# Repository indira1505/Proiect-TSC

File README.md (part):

INK TIME SMARTWATCH

1. DIAGRAMA COMPONENTE
    Acesta este un proiect de ceas inteligent bazat pe arhitectura nRF52840, echipat cu un ecran
e-Paper pentru consum redus și un sistem de alertă haptică.

2. Bill Of Materials

| Qty | Value                                  | Device                                                                       | Package                                                                                                                | Parts                                                                                                                      | Description                                                                                                               | ARROW_PART_NUMBER | ARROW_PRICE-STOCK                                                                                | AVAILABILITY | CHECK_PRICES                                                                       | COPYRIGHT                                                | DESCRIPTION                                                                                              | HEIGHT                                   | JLCPCB      | MANUFACTURER_NAME                                 | MANUFACTURER_PART_NUMBER                                         | MF                 | MFR_NAME          | MOUSER_PART_NUMBER | MOUSER_PRICE-STOCK                                                                                           | MP                                                                                                       | PACKAGE                     | POPULARITY | PRICE            | PROD_ID                      | PURCHASE-URL                                                                                                                               | SNAPEDA_LINK                                                                      | TP_SIGNAL_NAME | U1                                                                                                                                              | VALUE                                                                               |
|-----|----------------------------------------|------------------------------------------------------------------------------|------------------------------------------------------------------------------------------------------------------------|----------------------------------------------------------------------------------------------------------------------------|---------------------------------------------------------------------------------------------------------------------------|-------------------|--------------------------------------------------------------------------------------------------|--------------|------------------------------------------------------------------------------------|----------------------------------------------------------|----------------------------------------------------------------------------------------------------------|------------------------------------------|-------------|---------------------------------------------------|------------------------------------------------------------------|--------------------|-------------------|--------------------|--------------------------------------------------------------------------------------------------------------|----------------------------------------------------------------------------------------------------------|-----------------------------|------------|------------------|------------------------------|--------------------------------------------------------------------------------------------------------------------------------------------|-----------------------------------------------------------------------------------|----------------|-------------------------------------------------------------------------------------------------------------------------------------------------|-------------------------------------------------------------------------------------|
| 1   | RT6160AWSC                             | RT6160AWSC_RT6160AWSC                                                        | RT6160AWSC_BGA15C40P3X5_140X230X60                                                                                     | IC9                                                                                                                        | Buck-Boost Regulator Positive Output Step-Up/Step-Down I2C DC-DC Controller IC 15-WL-CSP (BSC) (1.4x2.3)                  |                   |                                                                                                  |              |                                                                                    |                                                          | Buck-Boost Regulator Positive Output Step-Up/Step-Down I2C DC-DC Controller IC 15-WL-CSP (BSC) (1.4x2.3) | 0.6mm                                    |             | RICHTEK                                           | RT6160AWSC                                                       |                    |                   | 835-RT6160AWSC     | https://www.mouser.co.uk/ProductDetail/Richtek/RT6160AWSC?qs=amGC7iS6iy%2FLd9PSoixZXQ%3D%3D                  |                                                                                                          |                             |            |                  |                              |                                                                                                                                            |                                                                                   |                |                                                                                                                                                 |                                                                                     |
| 1   | SI1308EDL-T1-GE3                       | ESP32_C6_LIBRARY_6_SI1308EDL-T1-GE3                                          | ESP32_C6_LIBRARY_6_SOT65P210X110-3N                                                                                    | Q3                                                                                                                         | MOSFET N-Ch 30V 1.5A TrenchFET SC70 Vishay Si1308EDL-T1-GE3 N-channel MOSFET Transistor, 1.5 A, 30 V, 3-Pin SC-70         |                   |                                                                                                  | In Stock     | https://www.snapeda.com/parts/SI1308EDL-T1-GE3/Vishay+Siliconix/view-part/?ref=eda |                                                          | Si1308EDL-T1-GE3 N-channel MOSFET Transistor                                                             | 1.5 A                                    | 30 V        | 3-Pin SC-70 | Siliconix / Vishay SI1308EDL-T1-GE3 |                                                                  |                    |                   |                    | Vishay Siliconix                                                                                             |                                                                                                          |                             |            | SI1308EDL-T1-GE3 | SOT-323 Vishay Semiconductor |                                                                                                                                            | None                                                                              |                | https://www.snapeda.com/api/url_track_click_mouser/?unipart_id=274603&manufacturer=Vishay Siliconix&part_name=SI1308EDL-T1-GE3&search_term=None | https://www.snapeda.com/parts/SI1308EDL-T1-GE3/Vishay+Siliconix/view-part/?ref=snap |
| 1   | TC2030-IDC                             | TC2030-IDC_TC2030-IDC                                                        | TC2030-IDC_TC2030IDC                                                                                                   | J2                                                                                                                         | CABLE ADAPTER 6 POS                                                                                                       |                   |                                                                                                  |              |                                                                                    |                                                          | CABLE ADAPTER 6 POS                                                                                      | 19mm                                     |             | Tag Connect                                       | TC2030-IDC                                                       |                    |                   |                    |                                                                                                              |                                                                                                          |                             |            |                  |                              |                                                                                                                                            |                                                                                   |                |                                                                                                                                                 |                                                                                     |
| 1   | USBLC6-2SC6Y                           | ESP32_C6_LIBRARY_3_USBLC6-2SC6Y                                              | ESP32_C6_LIBRARY_3_SOT95P280X145-6N                                                                                    | D3                                                                                                                         | Low Cap. ESD Protection Auto SOT-23-6 STMicroelectronics USBLC6-2SC6Y, Dual Uni-Directional TVS Diode Array, 6-Pin SOT-23 |                   |                                                                                                  | In Stock     | https://www.snapeda.com/parts/USBLC6-2SC6Y/STMicroelectronics/view-part/?ref=eda   |                                                          | 17V Clamp 5A (8/20µs) Ipp Tvs Diode Surface Mount SOT-23-6                                               |                                          |             |                                                   |                                                                  | STMicroelectronics |                   |                    |                                                                                                              | USBLC6-2SC6Y                                                                                             | SOT-23-6 STMicroelectronics |            | None             |                              |                                                                                                                                            | https://www.snapeda.com/parts/USBLC6-2SC6Y/STMicroelectronics/view-part/?ref=snap |                |                                                                                                                                                 |                                                                                     |
| 1   | 0.1uF/50V                              | NORDIC_NRF_3_CAPACITOR_0201_L                                                | NORDIC_NRF_3_RESC0201_L                                                                                                | EPD_C5                                                                                                                     | Generic chip capacitor                                                                                                    |                   |                                                                                                  |              |                                                                                    |                                                          |                                                                                                          |                                          |             |                                                   |                                                                  |                    |                   |                    |                                                                                                              |                                                                                                          |                             |            |                  |                              |                                                                                                                                            |                                                                                   |                |                                                                                                                                                 |                                                                                     |
| 1   | 0.47                                   | CPF0201D7K68C1_CPF0201D7K68C1                                                | CPF0201D7K68C1_0201                                                                                                    | R1_EP_DR                                                                                                                   | 7.68k 0201 Thin Film Surface Mount Fixed Resistor +/-0.5% 0.031W CPF0201D7K68C1                                           |                   |                                                                                                  |              |                                                                                    |                                                          |                                                                                                          |                                          |             |                                                   |                                                                  |                    |                   |                    |                                                                                                              |                                                                                                          |                             |            |                  |                              |                                                                                                                                            |                                                                                   |                |                                                                                                                                                 |                                                                                     |
| 1   | 1.0µF                                  | NORDIC_NRF_3_CAPACITOR_0201_L                                                | NORDIC_NRF_3_RESC0201_L                                                                                                | C15                                                                                                                        | Generic chip capacitor                                                                                                    |                   |                                                                                                  |              |                                                                                    |                                                          |                                                                                                          |                                          |             |                                                   |                                                                  |                    |                   |                    |                                                                                                              |                                                                                                          |                             |            |                  |                              |                                                                                                                                            |                                                                                   |                |                                                                                                                                                 |                                                                                     |
| 5   | 100nF                                  | NORDIC_NRF_3_CAPACITOR_0201_L                                                | NORDIC_NRF_3_RESC0201_L                                                                                                | C5, C7, C8, C12, C19                                                                                                       | Generic chip capacitor                                                                                                    |                   |                                                                                                  |              |                                                                                    |                                                          |                                                                                                          |                                          |             |                                                   |                                                                  |                    |                   |                    |                                                                                                              |                                                                                                          |                             |            |                  |                              |                                                                                                                                            |                                                                                   |                |                                                                                                                                                 |                                                                                     |
| 1   | 100pF                                  | NORDIC_NRF_3_CAPACITOR_0201_L                                                | NORDIC_NRF_3_RESC0201_L                                                                                                | C11                                                                                                                        | Generic chip capacitor                                                                                                    |                   |                                                                                                  |              |                                                                                    |                                                          |                                                                                                          |                                          |             |                                                   |                                                                  |                    |                   |                    |                                                                                                              |                                                                                                          |                             |            |                  |                              |                                                                                                                                            |                                                                                   |                |                                                                                                                                                 |                                                                                     |
| 4   | 0.1uF                                  | GRM011R60J152KE01L_2_GRM011R60J152KE01L                                      | GRM011R60J152KE01L_2_CAPC0201X13N                                                                                      | C23, C27, C34, C42                                                                                                         | Check availability                                                                                                        |                   |                                                                                                  | In Stock     | https://www.snapeda.com/parts/GRM011R60J152KE01L/Murata/view-part/?ref=eda         |                                                          | SMD Capacitor X5R(EIA) with Capacitance: 1500pF Tol. 10%. Rated Voltage: 6.3Vdc                          |                                          |             |                                                   |                                                                  | Murata             |                   |                    |                                                                                                              | GRM011R60J152KE01L                                                                                       | 0201 Murata                 |            | None             |                              |                                                                                                                                            | https://www.snapeda.com/parts/GRM011R60J152KE01L/Murata/view-part/?ref=snap       |                |                                                                                                                                                 |                                                                                     |
| 3   | 10K                                    | CPF0201D7K68C1_CPF0201D7K68C1                                                | CPF0201D7K68C1_0201                                                                                                    | R2_EP_DR, R9, R_PWR_EPD                                                                                                    | 7.68k 0201 Thin Film Surface Mount Fixed Resistor +/-0.5% 0.031W CPF0201D7K68C1                                           |                   |                                                                                                  |              |                                                                                    |                                                          |                                                                                                          |                                          |             |                                                   |                                                                  |                    |                   |                    |                                                                                                              |                                                                                                          |                             |            |                  |                              |                                                                                                                                            |                                                                                   |                |                                                                                                                                                 |                                                                                     |
| 3   | 10K                                    | ERA-1AEB3401C_CPF0201D7K68C1                                                 | ERA-1AEB3401C_0201                                                                                                     | R5, R7, R8                                                                                                                 | 7.68k 0201 Thin Film Surface Mount Fixed Resistor +/-0.5% 0.031W CPF0201D7K68C1                                           |                   |                                                                                                  |              |                                                                                    |                                                          |                                                                                                          |                                          |             |                                                   |                                                                  |                    |                   |                    |                                                                                                              |                                                                                                          |                             |            |                  |                              |                                                                                                                                            |                                                                                   |                |                                                                                                                                                 |                                                                                     |
| 1   | 10uF                                   | NORDIC_NRF_3_CAPACITOR_0201_L                                                | NORDIC_NRF_3_RESC0201_L                                                                                                | C1-EP-DR                                                                                                                   | Generic chip capacitor                                                                                                    |                   |                                                                                                  |              |                                                                                    |                                                          |                                                                                                          |                                          |             |                                                   |                                                                  |                    |                   |                    |                                                                                                              |                                                                                                          |                             |            |                  |                              |                                                                                                                                            |                                                                                   |                |                                                                                                                                                 |                                                                                     |
| 2   | 10uF                                   | PERFECT_0402_CAP_0402                                                        | PERFECT_0402_0402                                                                                                      | C24, C39                                                                                                                   | 0402 (1005 Metric)                                                                                                        |                   |                                                                                                  |              |                                                                                    |                                                          |                                                                                                          |                                          |             |                                                   |                                                                  |                    |                   |                    |                                                                                                              |                                                                                                          |                             |            |                  |                              |                                                                                                                                            |                                                                                   |                |                                                                                                                                                 |                                                                                     |
| 1   |                                        | ESP32_C6_LIBRARY_7_JUMPER_SJ                                                 | ESP32_C6_LIBRARY_7_JUMPER_SJ                                                                                           | SJ1                                                                                                                        | SMD solder JUMPER                                                                                                         |                   |                                                                                                  |              |                                                                                    |                                                          |                                                                                                          |                                          |             |                                                   |                                                                  |                    |                   |                    |                                                                                                              |                                                                                                          |                             | 3          |                  |                              |                                                                                                                                            |                                                                                   |                |                                                                                                                                                 |                                                                                     |
| 3   | 0                                      | CPF0201D7K68C1_CPF0201D7K68C1                                                | CPF0201D7K68C1_0201                                                                                                    | R2, R3, R4                                                                                                                 | 7.68k 0201 Thin Film Surface Mount Fixed Resistor +/-0.5% 0.031W CPF0201D7K68C1                                           |                   |                                                                                                  |              |                                                                                    |                                                          |                                                                                                          |                                          |             |                                                   |                                                                  |                    |                   |                    |                                                                                                              |                                                                                                          |                             |            |                  |                              |                                                                                                                                            |                                                                                   |                |                                                                                                                                                 |                                                                                     |
| 1   | 10µH                                   | NORDIC_NRF_2_INDUCTOR_0402_L                                                 | NORDIC_NRF_2_RESC0402_L                                                                                                | L2                                                                                                                         | Generic chip inductor                                                                                                     |                   |                                                                                                  |              |                                                                                    |                                                          |                                                                                                          |                                          |             |                                                   |                                                                  |                    |                   |                    |                                                                                                              |                                                                                                          |                             |            |                  |                              |                                                                                                                                            |                                                                                   |                |                                                                                                                                                 |                                                                                     |
| 4   | 12pF                                   | NORDIC_NRF_3_CAPACITOR_0201_L                                                | NORDIC_NRF_3_RESC0201_L                                                                                                | C1, C2, C17, C18                                                                                                           | Generic chip capacitor                                                                                                    |                   |                                                                                                  |              |                                                                                    |                                                          |                                                                                                          |                                          |             |                                                   |                                                                  |                    |                   |                    |                                                                                                              |                                                                                                          |                             |            |                  |                              |                                                                                                                                            |                                                                                   |                |                                                                                                                                                 |                                                                                     |
| 1   | 15nH                                   | NORDIC_NRF_2_INDUCTOR_0402_L                                                 | NORDIC_NRF_2_RESC0402_L                                                                                                | L3                                                                                                                         | Generic chip inductor                                                                                                     |                   |                                                                                                  |              |                                                                                    |                                                          |                                                                                                          |                                          |             |                                                   |                                                                  |                    |                   |                    |                                                                                                              |                                                                                                          |                             |            |                  |                              |                                                                                                                                            |                                                                                   |                |                                                                                                                                                 |                                                                                     |
| 2   | 1pF                                    | NORDIC_NRF_3_CAPACITOR_0201_L                                                | NORDIC_NRF_3_RESC0201_L                                                                                                | C3, C4                                                                                                                     | Generic chip capacitor                                                                                                    |                   |                                                                                                  |              |                                                                                    |                                                          |                                                                                                          |                                          |             |                                                   |                                                                  |                    |                   |                    |                                                                                                              |                                                                                                          |                             |            |                  |                              |                                                                                                                                            |                                                                                   |                |                                                                                                                                                 |                                                                                     |
| 6   | 1uF                                    | GRM011R60J152KE01L_2_GRM011R60J152KE01L                                      | GRM011R60J152KE01L_2_CAPC0201X13N                                                                                      | C29, C30, C31, C32, C37, C38                                                                                               | Check availability                                                                                                        |                   |                                                                                                  | In Stock     | https://www.snapeda.com/parts/GRM011R60J152KE01L/Murata/view-part/?ref=eda         |                                                          | SMD Capacitor X5R(EIA) with Capacitance: 1500pF Tol. 10%. Rated Voltage: 6.3Vdc                          |                                          |             |                                                   |                                                                  | Murata             |                   |                    |                                                                                                              | GRM011R60J152KE01L                                                                                       | 0201 Murata                 |            | None             |                              |                                                                                                                                            | https://www.snapeda.com/parts/GRM011R60J152KE01L/Murata/view-part/?ref=snap       |                |                                                                                                                                                 |                                                                                     |
| 9   | 1uF/50V                                | NORDIC_NRF_3_CAPACITOR_0201_L                                                | NORDIC_NRF_3_RESC0201_L                                                                                                | EPD_C1, EPD_C2, EPD_C6, EPD_C7, EPD_C8, EPD_C9, EPD_C10, EPD_C11, EPD_C12                                                  | Generic chip capacitor                                                                                                    |                   |                                                                                                  |              |                                                                                    |                                                          |                                                                                                          |                                          |             |                                                   |                                                                  |                    |                   |                    |                                                                                                              |                                                                                                          |                             |            |                  |                              |                                                                                                                                            |                                                                                   |                |                                                                                                                                                 |                                                                                     |
| 1   | 2.2                                    | CPF0201D7K68C1_CPF0201D7K68C1                                                | CPF0201D7K68C1_0201                                                                                                    | R_TYPE_SEL                                                                                                                 | 7.68k 0201 Thin Film Surface Mount Fixed Resistor +/-0.5% 0.031W CPF0201D7K68C1                                           |                   |                                                                                                  |              |                                                                                    |                                                          |                                                                                                          |                                          |             |                                                   |                                                                  |                    |                   |                    |                                                                                                              |                                                                                                          |                             |            |                  |                              |                                                                                                                                            |                                                                                   |                |                                                                                                                                                 |                                                                                     |
| 3   | 2025-10-22_07-23-44_LIBRARY_EVP-AKE31A | 2025-10-22_07-23-44_LIBRARY_EVP-AKE31A                                       | 2025-10-22_07-23-44_LIBRARY_SW_EVP-AKE31A_PAN                                                                          | SW_DN, SW_ENT, SW_UP                                                                                                       |                                                                                                                           |                   |                                                                                                  |              |                                                                                    |                                                          |                                                                                                          |                                          |             |                                                   |                                                                  |                    |                   |                    |                                                                                                              |                                                                                                          |                             |            |                  |                              |                                                                                                                                            |                                                                                   |                |                                                                                                                                                 |                                                                                     |
| 1   | 20V/4.2A/52mΩ/1.4W                     | ESP32_C6_LIBRARY_4_ESP32_WROVER_SPARKFUN-DISCRETESEMI_MOSFET_PCH-DMG2305UX-7 | ESP32_C6_LIBRARY_4_ESP32_C6_LIBRARY_4_ESP32_C6_LIBRARY_4_ESP32_C6_LIBRARY_4_ESP32_WROVER_SPARKFUN-DISCRETESEMI_SOT23-3 | Q1                                                                                                                         | P-channel MOSFETs                                                                                                         |                   |                                                                                                  |              |                                                                                    |                                                          |                                                                                                          |                                          |             |                                                   |                                                                  |                    |                   |                    |                                                                                                              |                                                                                                          |                             |            |                  | TRAN-14388                   |                                                                                                                                            |                                                                                   |                |                                                                                                                                                 | 20V/4.2A/52mΩ/1.4W                                                                  |
| 2   | 22uF                                   | PERFECT_0402_CAP_0402                                                        | PERFECT_0402_0402                                                                                                      | C25, C33                                                                                                                   | 0402 (1005 Metric)                                                                                                        |                   |                                                                                                  |              |                                                                                    |                                                          |                                                                                                          |                                          |             |                                                   |                                                                  |                    |                   |                    |                                                                                                              |                                                                                                          |                             |            |                  |                              |                                                                                                                                            |                                                                                   |                |                                                                                                                                                 |                                                                                     |
| 1   | 2450AT18B100E                          | 2450AT18B100E_2450AT18B100E                                                  | 2450AT18B100E_ANTC3216X140N                                                                                            | ANT1                                                                                                                       | Antennas 2.45GHz ANTENNA                                                                                                  | 2450AT18B100E     | https://www.arrow.com/en/products/2450at18b100e/johanson-dielectrics?utm_currency=USD&region=nac |              |                                                                                    |                                                          | Antennas 2.45GHz ANTENNA                                                                                 | 1.4mm                                    |             | JOHANSON TECHNOLOGY                               | 2450AT18B100E                                                    |                    |                   | 609-2450AT18B100E  | https://www.mouser.co.uk/ProductDetail/Johanson-Technology/2450AT18B100E?qs=yCnrNFeXz%252Bh5MFsFIXGZGA%3D%3D |                                                                                                          |                             |            |                  |                              |                                                                                                                                            |                                                                                   |                |                                                                                                                                                 |                                                                                     |
| 1   | 3.9nH                                  | NORDIC_NRF_2_INDUCTOR_0402_L                                                 | NORDIC_NRF_2_RESC0402_L                                                                                                | L1                                                                                                                         | Generic chip inductor                                                                                                     |                   |                                                                                                  |              |                                                                                    |                                                          |                                                                                                          |                                          |             |                                                   |                                                                  |                    |                   |                    |                                                                                                              |                                                                                                          |                             |            |                  |                              |                                                                                                                                            |                                                                                   |                |                                                                                                                                                 |                                                                                     |
| 1   | 32.768kHz                              | NORDIC_NRF_1_XTAL_32KHZ                                                      | NORDIC_NRF_1_XTAL_3215_N                                                                                               | X2                                                                                                                         |                                                                                                                           |                   |                                                                                                  |              |                                                                                    |                                                          |                                                                                                          |                                          |             |                                                   |                                                                  |                    |                   |                    |                                                                                                              |                                                                                                          |                             |            |                  |                              |                                                                                                                                            |                                                                                   |                |                                                                                                                                                 |                                                                                     |
| 1   | 32MHz                                  | NORDIC_NRF_XTAL_32MHZ                                                        | NORDIC_NRF_BT-XTAL_2016_N                                                                                              | X1                                                                                                                         |                                                                                                                           |                   |                                                                                                  |              |                                                                                    |                                                          |                                                                                                          |                                          |             |                                                   |                                                                  |                    |                   |                    |                                                                                                              |                                                                                                          |                             |            |                  |                              |                                                                                                                                            |                                                                                   |                |                                                                                                                                                 |                                                                                     |
| 2   | 3K3                                    | CPF0201D7K68C1_CPF0201D7K68C1                                                | CPF0201D7K68C1_0201                                                                                                    | R17, R18                                                                                                                   | 7.68k 0201 Thin Film Surface Mount Fixed Resistor +/-0.5% 0.031W CPF0201D7K68C1                                           |                   |                                                                                                  |              |                                                                                    |                                                          |                                                                                                          |                                          |             |                                                   |                                                                  |                    |                   |                    |                                                                                                              |                                                                                                          |                             |            |                  |                              |                                                                                                                                            |                                                                                   |                |                                                                                                                                                 |                                                                                     |
| 1   | 4.7uF                                  | NORDIC_NRF_3_CAPACITOR_0201_L                                                | NORDIC_NRF_3_RESC0201_L                                                                                                | C43                                                                                                                        | Generic chip capacitor                                                                                                    |                   |                                                                                                  |              |                                                                                    |                                                          |                                                                                                          |                                          |             |                                                   |                                                                  |                    |                   |                    |                                                                                                              |                                                                                                          |                             |            |                  |                              |                                                                                                                                            |                                                                                   |                |                                                                                                                                                 |                                                                                     |
| 1   | 4.7uF/25V                              | NORDIC_NRF_3_CAPACITOR_0201_L                                                | NORDIC_NRF_3_RESC0201_L                                                                                                | C2-EP-DR                                                                                                                   | Generic chip capacitor                                                                                                    |                   |                                                                                                  |              |                                                                                    |                                                          |                                                                                                          |                                          |             |                                                   |                                                                  |                    |                   |                    |                                                                                                              |                                                                                                          |                             |            |                  |                              |                                                                                                                                            |                                                                                   |                |                                                                                                                                                 |                                                                                     |
| 4   | 4.7µF                                  | NORDIC_NRF_3_CAPACITOR_0201_L                                                | NORDIC_NRF_3_RESC0201_L                                                                                                | C6, C14, C20, C21                                                                                                          | Generic chip capacitor                                                                                                    |                   |                                                                                                  |              |                                                                                    |                                                          |                                                                                                          |                                          |             |                                                   |                                                                  |                    |                   |                    |                                                                                                              |                                                                                                          |                             |            |                  |                              |                                                                                                                                            |                                                                                   |                |                                                                                                                                                 |                                                                                     |
| 1   | 47nF                                   | NORDIC_NRF_3_CAPACITOR_0201_L                                                | NORDIC_NRF_3_RESC0201_L                                                                                                | C16                                                                                                                        | Generic chip capacitor                                                                                                    |                   |                                                                                                  |              |                                                                                    |                                                          |                                                                                                          |                                          |             |                                                   |                                                                  |                    |                   |                    |                                                                                                              |                                                                                                          |                             |            |                  |                              |                                                                                                                                            |                                                                                   |                |                                                                                                                                                 |                                                                                     |
| 1   | 503480-2400                            | 503480-2400_503480-2400                                                      | 503480-2400_5034802400                                                                                                 | J1                                                                                                                         | FFC & FPC Connectors 0.5mm FPC RA SMT Dual Contact 24Ckt                                                                  |                   |                                                                                                  |              |                                                                                    |                                                          | FFC & FPC Connectors 0.5mm FPC RA SMT Dual Contact 24Ckt                                                 | 1.87mm                                   |             | Molex                                             | 503480-2400                                                      |                    |                   | 538-503480-2400    | https://www.mouser.co.uk/ProductDetail/Molex/503480-2400?qs=OAhjpuo3Vu7efIoxFh9AOw%3D%3D                     |                                                                                                          |                             |            |                  |                              |                                                                                                                                            |                                                                                   |                |                                                                                                                                                 |                                                                                     |
| 2   | 5K1                                    | CPF0201D7K68C1_CPF0201D7K68C1                                                | CPF0201D7K68C1_0201                                                                                                    | R1_USB, R2_USB                                                                                                             | 7.68k 0201 Thin Film Surface Mount Fixed Resistor +/-0.5% 0.031W CPF0201D7K68C1                                           |                   |                                                                                                  |              |                                                                                    |                                                          |                                                                                                          |                                          |             |                                                   |                                                                  |                    |                   |                    |                                                                                                              |                                                                                                          |                             |            |                  |                              |                                                                                                                                            |                                                                                   |                |                                                                                                                                                 |                                                                                     |
| 1   | 68uH                                   | ESP32_C6_LIBRARY_2_744043680IND_4828-WE-TPC_WRE                              | ESP32_C6_LIBRARY_2_IND_4828-WE-TPC_WRE                                                                                 | L5                                                                                                                         |                                                                                                                           |                   |                                                                                                  |              |                                                                                    | Copyright (C) 2024 Ultra Librarian. All rights reserved. |                                                                                                          |                                          |             |                                                   | 744043680                                                        |                    | Wurth Electronics |                    |                                                                                                              |                                                                                                          |                             |            |                  |                              |                                                                                                                                            |                                                                                   |                |                                                                                                                                                 |                                                                                     |
| 1   | 820pF N.C.                             | NORDIC_NRF_3_CAPACITOR_0201_L                                                | NORDIC_NRF_3_RESC0201_L                                                                                                | C9                                                                                                                         | Generic chip capacitor                                                                                                    |                   |                                                                                                  |              |                                                                                    |                                                          |                                                                                                          |                                          |             |                                                   |                                                                  |                    |                   |                    |                                                                                                              |                                                                                                          |                             |            |                  |                              |                                                                                                                                            |                                                                                   |                |                                                                                                                                                 |                                                                                     |
| 1   | BMA421                                 | BMA423_BMA423                                                                | BMA423_BMA423                                                                                                          | IC3                                                                                                                        | Accelerometers Triaxial low-g 12bit Acceleration Sensor                                                                   | BMA423            | https://www.arrow.com/en/products/bma423/bosch                                                   |              |                                                                                    |                                                          | Accelerometers Triaxial low-g 12bit Acceleration Sensor                                                  | 1mm                                      |             | BOSCH                                             | BMA423                                                           |                    |                   | 262-BMA423         | https://www.mouser.co.uk/ProductDetail/Bosch-Sensortec/BMA423?qs=HXFqYaX1Q2xC%252BSgeGoX3mg%3D%3D            |                                                                                                          |                             |            |                  |                              |                                                                                                                                            |                                                                                   |                |                                                                                                                                                 |                                                                                     |
| 1   | BQ25180YBGR                            | BQ25180YBGR_BQ25180YBGR                                                      | BQ25180YBGR_BGA8C40P2X4_100X155X50                                                                                     | IC1                                                                                                                        | Charger IC Lithium Ion/Polymer, Lithium Iron Phosphate 8-DSBGA (1.6x1.1)                                                  | BQ25180YBGR       | https://www.arrow.com/en/products/bq25180ybgr/texas-instruments?utm_currency=USD&region=nac      |              |                                                                                    |                                                          | Charger IC Lithium Ion/Polymer                                                                           | Lithium Iron Phosphate 8-DSBGA (1.6x1.1) | 0.5mm       |                                                   | Texas Instruments                                                | BQ25180YBGR        |                   |                    | 595-BQ25180YBGR                                                                                              | https://www.mouser.co.uk/ProductDetail/Texas-Instruments/BQ25180YBGR?qs=doiCPypUmgEWjAK%252BJAX6Tw%3D%3D |                             |            |                  |                              |                                                                                                                                            |                                                                                   |                |                                                                                                                                                 |                                                                                     |
| 1   | DRV2605YZFR                            | DRV2605YZFR_DRV2605YZFR                                                      | DRV2605YZFR_BGA9C50P3X3_144X144X62                                                                                     | IC2                                                                                                                        | Haptic Driver for ERM/LRA with Built-In Library and Smart Loop Architecture                                               | DRV2605YZFR       | https://www.arrow.com/en/products/drv2605yzfr/texas-instruments?region=nac                       |              |                                                                                    |                                                          | Haptic Driver for ERM/LRA with Built-In Library and Smart Loop Architecture                              | 0.625mm                                  |             | Texas Instruments                                 | DRV2605YZFR                                                      |                    |                   |                    |                                                                                                              |                                                                                                          |                             |            |                  |                              |                                                                                                                                            |                                                                                   |                |                                                                                                                                                 |                                                                                     |
| 1   | FTC252012SR47MBCA                      | MLP2016SR47MT0S1_FTC252012SR47MBCA                                           | MLP2016SR47MT0S1_INDC2016X100N                                                                                         | L7                                                                                                                         | SMD / SMT Inductors (Coils), L=0.47?H, L x W x T :                                                                        |                   |                                                                                                  |              |                                                                                    |                                                          | SMD / SMT Inductors (Coils)                                                                              | L=0.47?H                                 | L x W x T : | 1mm                                               | https://jlcpcb.com/partdetail/6763488-FTC252012SR47MBCA/C5832368 | TDK                | FTC252012SR47MBCA |                    |                                                                                                              |                                                                                                          |                             |            |                  |                              |                                                                                                                                            |                                                                                   |                |                                                                                                                                                 |                                                                                     |
| 14  | HECTOR_WATCH_1_TPTP20R                 | HECTOR_WATCH_1_TPTP20R                                                       | HECTOR_WATCH_1_TP20R                                                                                                   | TP_3.3V, TP_3V3, TP_BAT_GND, TP_GND, TP_ON, TP_OP, TP_RESET, TP_SCL, TP_SDA, TP_SWDCLK, TP_SWDIO, TP_SWO, TP_VBAT, TP_VREG | Test pad                                                                                                                  |                   |                                                                                                  |              |                                                                                    |                                                          |                                                                                                          |                                          |             |                                                   |                                                                  |                    |                   |                    |                                                                                                              |                                                                                                          |                             | 2          |                  |                              |                                                                                                                                            |                                                                                   |                |                                                                                                                                                 |                                                                                     |
| 1   | KH-TYPE-C-16P                          | KH-TYPE-C-16P_KH-TYPE-C-16P                                                  | KH-TYPE-C-16P_KINGHELM_KH-TYPE-C-16P                                                                                   | J4                                                                                                                         | Check availability                                                                                                        |                   |                                                                                                  | Not in stock | https://www.snapeda.com/parts/KH-TYPE-C-16P/Kinghelm/view-part/?ref=eda            |                                                          |                                                                                                          |                                          |             |                                                   |                                                                  | kinghelm           |                   |                    |                                                                                                              | KH-TYPE-C-16P                                                                                            | None                        |            | None             |                              |                                                                                                                                            | https://www.snapeda.com/parts/KH-TYPE-C-16P/Kinghelm/view-part/?ref=snap          |                |                                                                                                                                                 |                                                                                     |
| 1   | MAX17048G+T10                          | ESP32_C6_LIBRARY_MAX17048G+T10                                               | ESP32_C6_LIBRARY_SON50P200X200X80-9N                                                                                   | U2                                                                                                                         | Check availability                                                                                                        |                   |                                                                                                  | In Stock     | https://www.snapeda.com/parts/MAX17048G+T10/Analog+Devices/view-part/?ref=eda      |                                                          | 3µA 1-Cell/2-Cell Fuel Gauge with ModelGauge                                                             |                                          |             |                                                   |                                                                  | Analog Devices     |                   |                    |                                                                                                              | MAX17048G+T10                                                                                            | TDFN-8 Maxim                |            | None             |                              | https://www.snapeda.com/api/url_track_click_mouser/?unipart_id=329239&manufacturer=Analog Devices&part_name=MAX17048G+T10&search_term=None | https://www.snapeda.com/parts/MAX17048G+T10/Analog+Devices/view-part/?ref=snap    |                |                                                                                                                                                 |                                                                                     |
| 3   | MBR0530                                | ESP32_C6_LIBRARY_5_MBR0530                                                   | ESP32_C6_LIBRARY_5_SOD3716X135N                                                                                        | D2, D4, D5                                                                                                                 | ON SEMICONDUCTOR - MBR0530 - DIODE, SCHOTTKY, 0.5A, 30V, SOD-123                                                          |                   |                                                                                                  | In Stock     | https://www.snapeda.com/parts/MBR0530/Onsemi/view-part/?ref=eda                    |                                                          | Diode Schottky 30 V 500mA Surface Mount SOD-123                                                          |                                          |             |                                                   |                                                                  | ON Semiconductor   |                   |                    |                                                                                                              | MBR0530                                                                                                  | SOD-123-2 ON Semiconductor  |            | None             |                              | https://www.snapeda.com/api/url_track_click_mouser/?unipart_id=179458&manufacturer=ON Semiconductor&part_name=MBR0530&search_term=None     | https://www.snapeda.com/parts/MBR0530/Onsemi/view-part/?ref=snap                  |                |                                                                                                                                                 |                                                                                     |
| 3   | N.C.                                   | NORDIC_NRF_3_CAPACITOR_0201_L                                                | NORDIC_NRF_3_RESC0201_L                                                                                                | C10, C13, C22                                                                                                              | Generic chip capacitor                                                                                                    |                   |                                                                                                  |              |                                                                                    |                                                          |                                                                                                          |                                          |             |                                                   |                                                                  |                    |                   |                    |                                                                                                              |                                                                                                          |                             |            |                  |                              |                                                                                                                                            |                                                                                   |                |                                                                                                                                                 |                                                                                     |
| 1   | NRF52840 _QF                           | NORDIC_NRF_4_NRF52840_QF                                                     | NORDIC_NRF_4_AQFN50P700X700X85_HS-74N                                                                                  | U1                                                                                                                         | nRF52840                                                                                                                  |                   |                                                                                                  |              |                                                                                    |                                                          |                                                                                                          |                                          |             |                                                   |                                                                  |                    |                   |                    |                                                                                                              |                                                                                                          |                             |            |                  |                              |                                                                                                                                            |                                                                                   |                | NRF52840 _QF                                                                                                                                    |                                                                                     |

3. DESCRIEREA FUNCTIONALITATII HARDWARE

Sistemul este construit in jurul SoC-ului nRF52840, fiind optimizat pentru un consum ultra-scazut de energie si securitate hardware.

Module si Componente Cheie:
Microcontroller (nRF52840): Procesor ARM Cortex-M4F cu unitate de criptare hardware CryptoCell-310. Acesta gestioneaza stack-ul Bluetooth Low Energy (BLE) si coordoneaza toate perifericele.

Sistemul de Putere (Power Tree):

BQ25180: IC de incarcare cu Power Path. Permite incarcarea bateriei LiPo si alimentarea simultana a sistemului.

MAX17048: Fuel Gauge (indicator nivel baterie). Masoara precis starea de incarcare (SoC) si tensiunea bateriei, comunicand prin I2C.

RT6160: Regulator Buck-Boost care asigura o tensiune stabila de 3.3V indiferent de nivelul de descarcare al bateriei.

Senzor de Miscare (BMA421): Accelerometru triaxial de mica putere. Este folosit pentru pedometru (numararea pasilor) si detectarea gesturilor (ex: "tilt-to-wake").

Afisaj e-Paper (1.54"): Display de tip "Electronic Ink" care consuma curent doar la refresh. Include un circuit de protectie cu un PFET (SI2301CDS) pentru a opri complet alimentarea ecranului in standby, eliminand scurgerile de curent.

Driver Haptic (DRV2605L): Controleaza motorul de vibratii (Shaker) folosind librarii de efecte pre-programate pentru un feedback tactil premium.

Cristal 32 MHz (X1): Esențial pentru funcționarea blocului radio (Bluetooth). Acesta oferă referința de înaltă frecvență necesară pentru stabilitatea semnalului și procesarea rapidă a datelor.

Cristal 32.768 kHz (X2): Componentă critică pentru optimizarea consumului. Acesta permite funcționarea ceasului de timp real (RTC) în modurile de Deep Sleep, menținând precizia timpului cu un consum infim de energie, fără a fi nevoie de oscilatorul intern RC (care este mai puțin precis și consumă mai mult).

Antena: Sistemul utilizează o antenă de tip traseu pe cablaj (Trace Antenna), calculată pentru frecvența de 2.4 GHz (Bluetooth Low Energy).Pentru a asigura o rază de acțiune maximă, s-a respectat o zonă de "Keep-out" (fără cupru) pe toate straturile sub antenă, prevenind astfel atenuarea semnalului.

Interfete de Comunicatie:
I2C (SDA/SCL): Magistrala principala de senzori unde sunt conectate: BMA421, DRV2605L, BQ25180 si MAX17048.

SPI: Interfata de mare viteza folosita exclusiv pentru ecranul e-Paper.

PWM: Folosit pentru controlul intensitatii vibratiilor shaker-ului.

Procesare si Energie:
Procesare: Cipul ruleaza la 64MHz, dar sta majoritatea timpului in Syst
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
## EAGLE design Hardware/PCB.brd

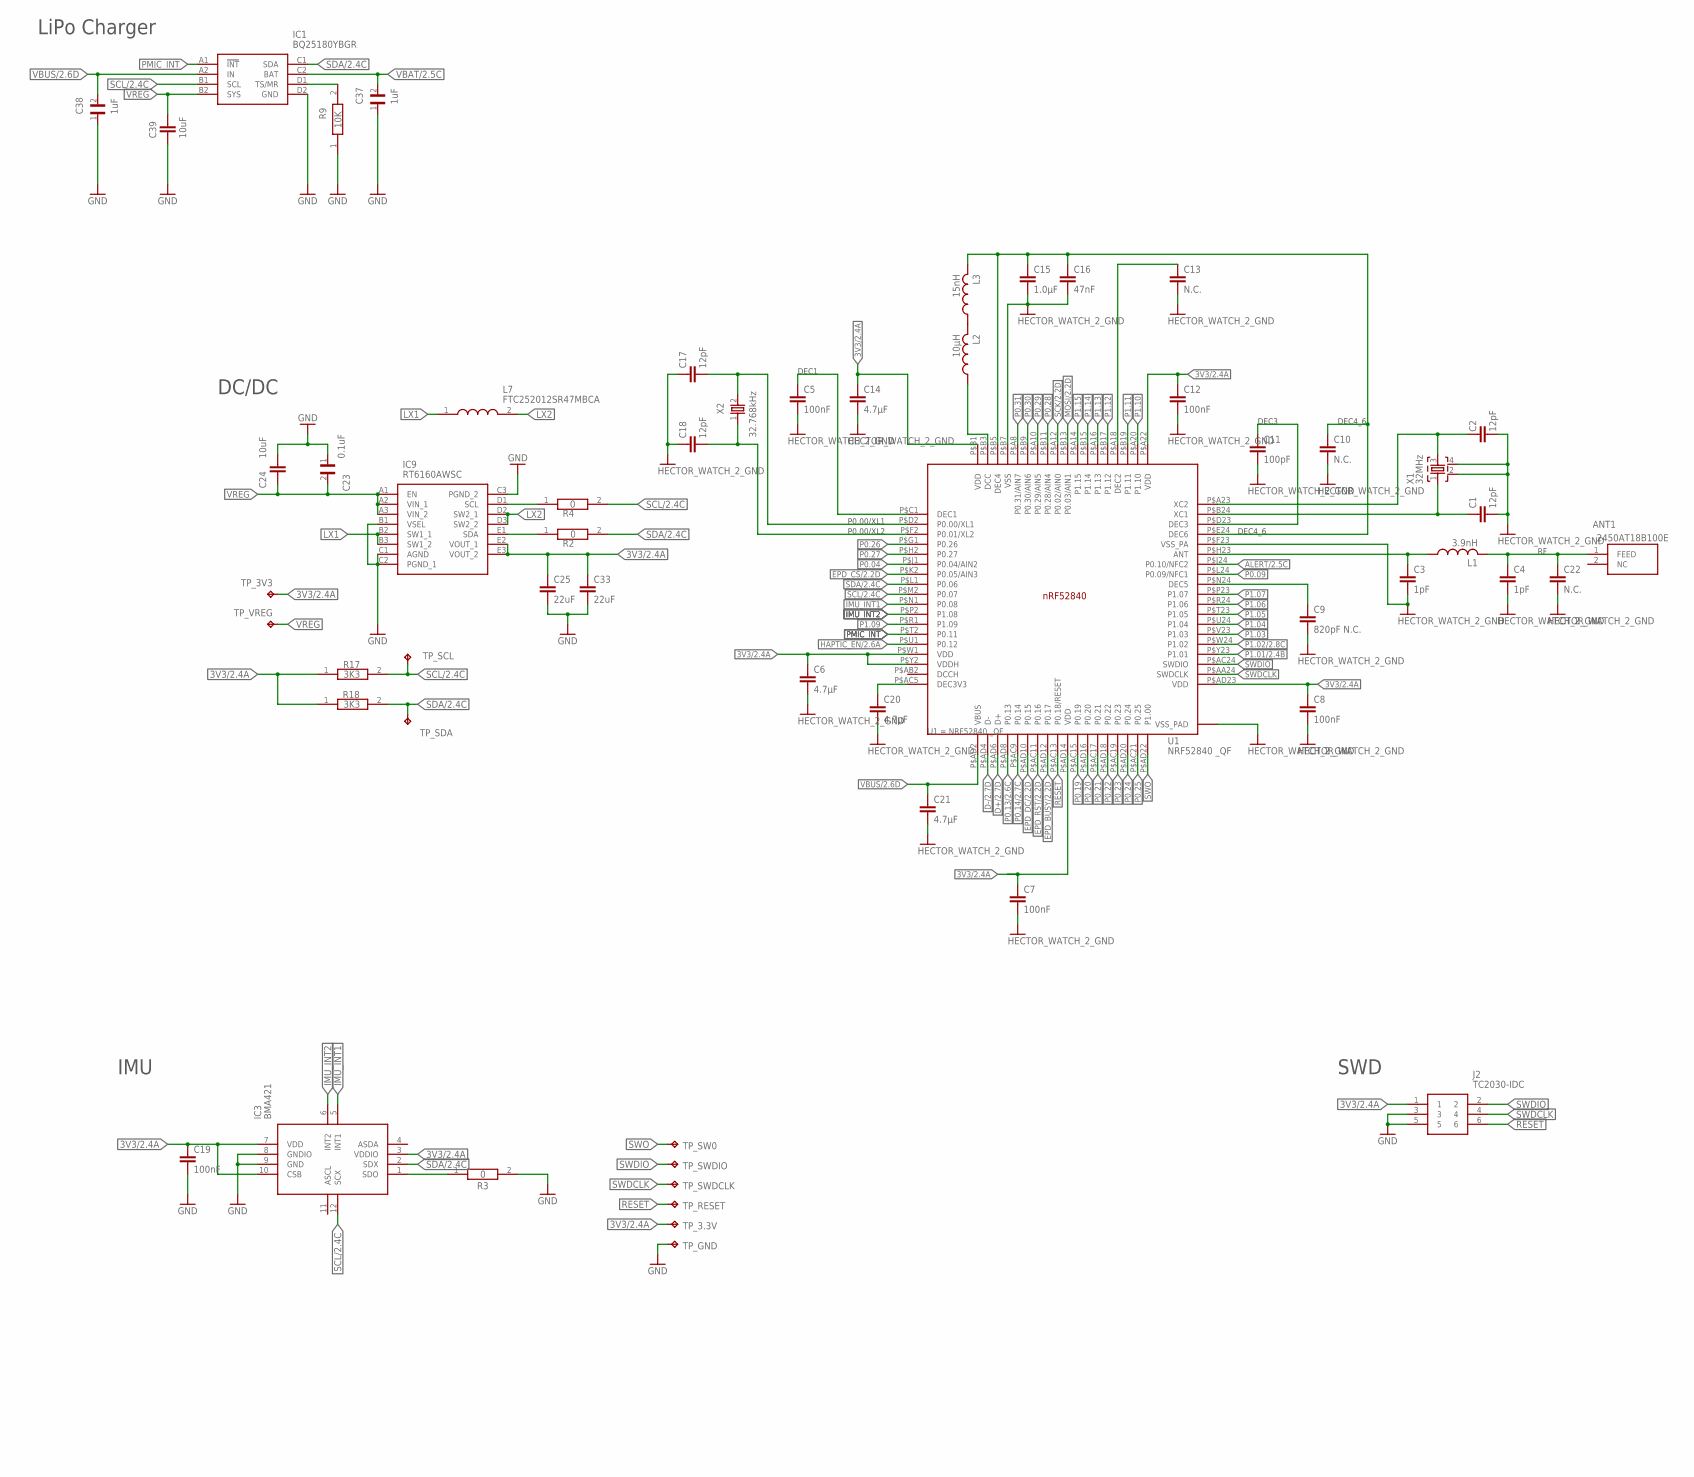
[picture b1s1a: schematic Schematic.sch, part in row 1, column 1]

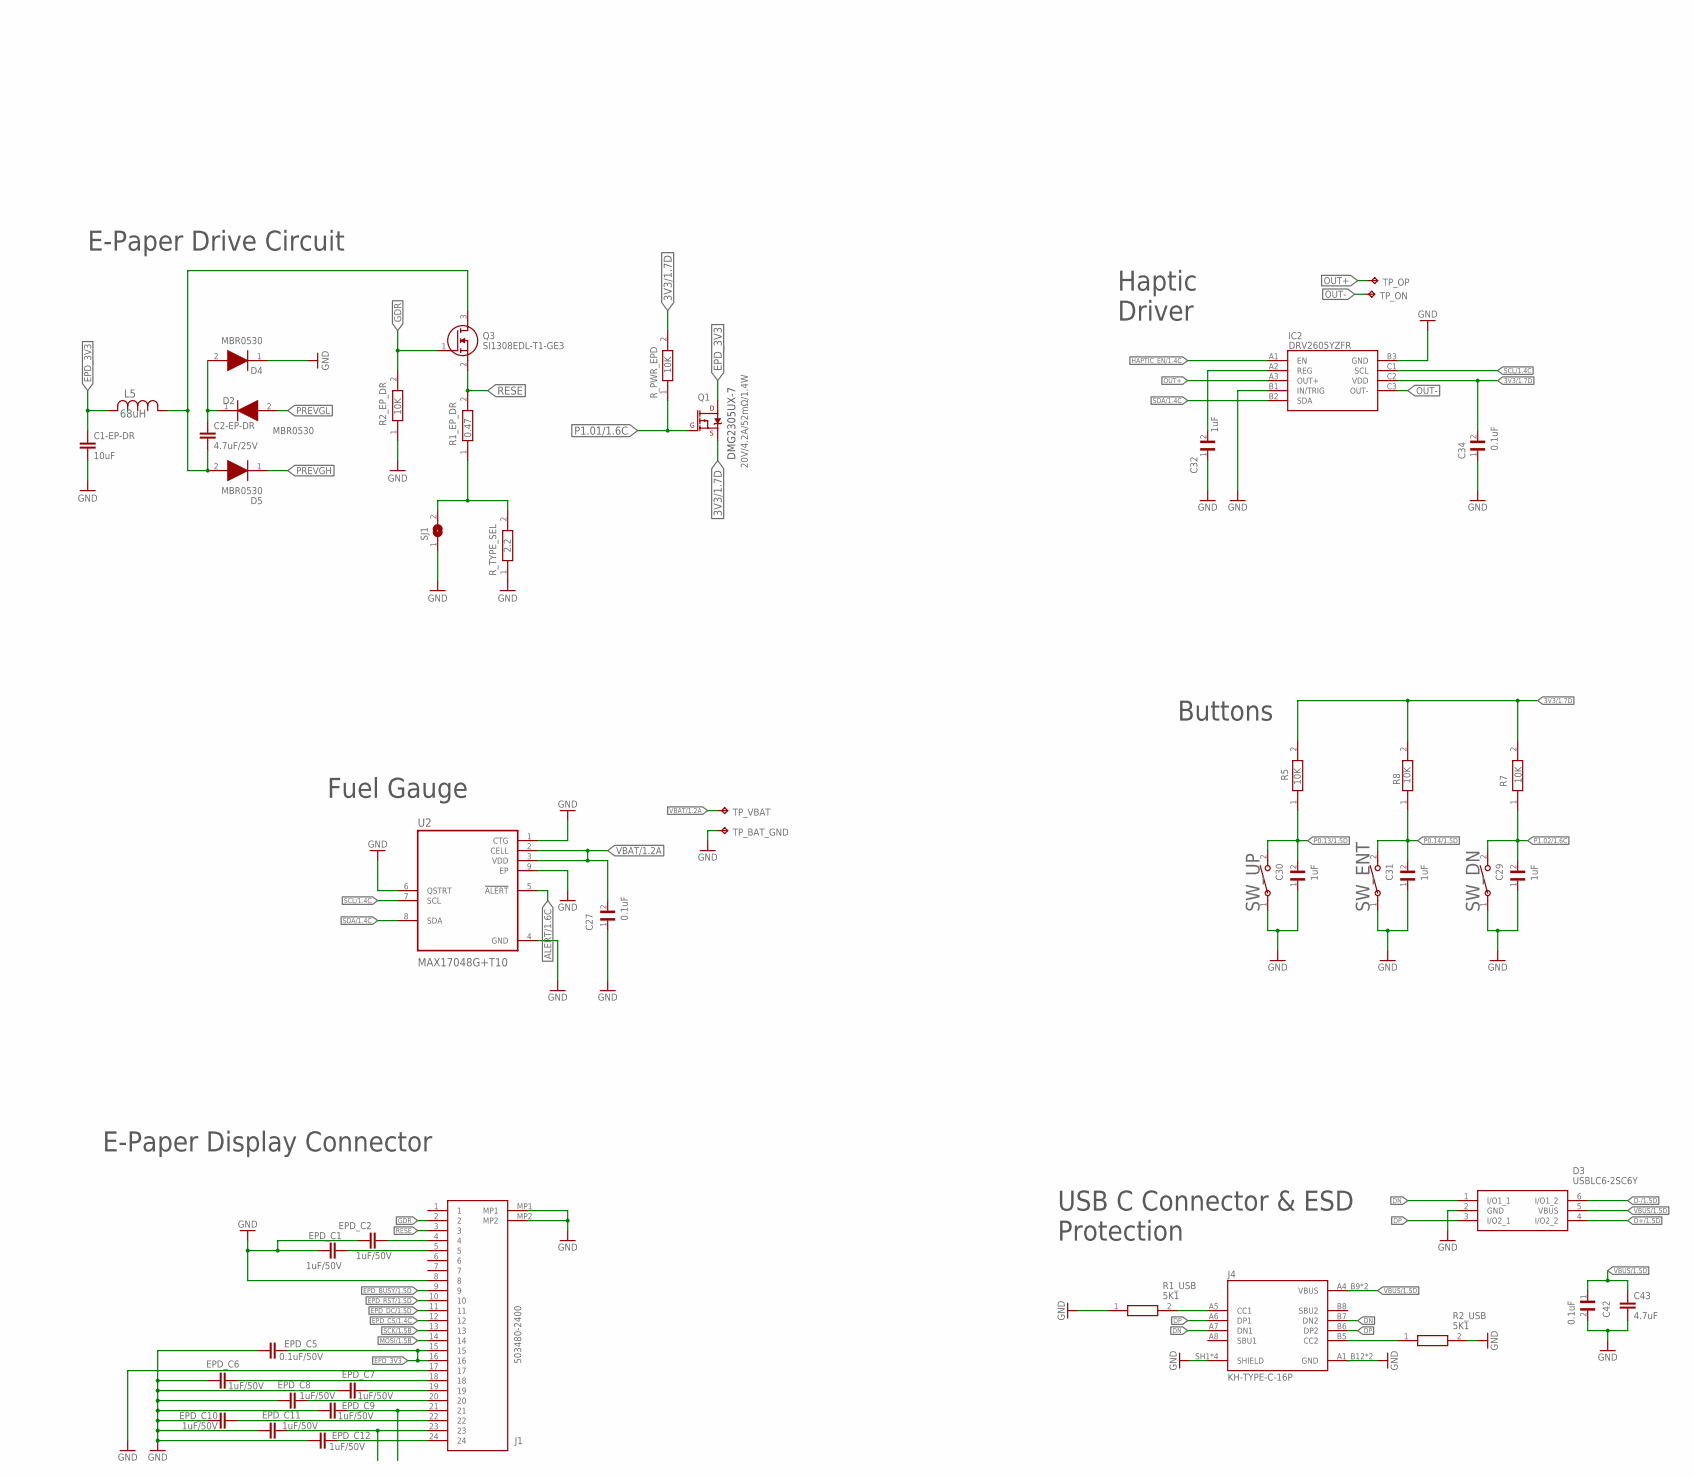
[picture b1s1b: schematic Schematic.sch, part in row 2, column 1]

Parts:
ANT1: 2450AT18B100E; 2450AT18B100E_ANTC3216X140N
C1, C2, C17, C18: 12pF; NORDIC_NRF_3_RESC0201_L
C1-EP-DR: 10uF; NORDIC_NRF_3_RESC0201_L
C2-EP-DR: 4.7uF/25V; NORDIC_NRF_3_RESC0201_L
C3, C4: 1pF; NORDIC_NRF_3_RESC0201_L
C5, C7, C8, C12, C19: 100nF; NORDIC_NRF_3_RESC0201_L
C6, C14, C20, C21: 4.7µF; NORDIC_NRF_3_RESC0201_L
C9: 820pF N.C.; NORDIC_NRF_3_RESC0201_L
C10, C13, C22: N.C.; NORDIC_NRF_3_RESC0201_L
C11: 100pF; NORDIC_NRF_3_RESC0201_L
C15: 1.0µF; NORDIC_NRF_3_RESC0201_L
C16: 47nF; NORDIC_NRF_3_RESC0201_L
C23, C27, C34, C42: 0.1uF; GRM011R60J152KE01L_2_CAPC0201X13N
C24, C39: 10uF; PERFECT_0402_0402
C25, C33: 22uF; PERFECT_0402_0402
C29, C30, C31, C32, C37, C38: 1uF; GRM011R60J152KE01L_2_CAPC0201X13N
C43: 4.7uF; NORDIC_NRF_3_RESC0201_L
D2, D4, D5: MBR0530; ESP32_C6_LIBRARY_5_SOD3716X135N
D3: USBLC6-2SC6Y; ESP32_C6_LIBRARY_3_SOT95P280X145-6N
EPD_C1, EPD_C2, EPD_C6, EPD_C7, EPD_C8, EPD_C9, EPD_C10, EPD_C11, EPD_C12: 1uF/50V; NORDIC_NRF_3_RESC0201_L
EPD_C5: 0.1uF/50V; NORDIC_NRF_3_RESC0201_L
IC1: BQ25180YBGR; BQ25180YBGR_BGA8C40P2X4_100X155X50
IC2: DRV2605YZFR; DRV2605YZFR_BGA9C50P3X3_144X144X62
IC3: BMA421; BMA423_BMA423
IC9: RT6160AWSC; RT6160AWSC_BGA15C40P3X5_140X230X60
J1: 503480-2400; 503480-2400_5034802400
J2: TC2030-IDC; TC2030-IDC_TC2030IDC
J4: KH-TYPE-C-16P; KH-TYPE-C-16P_KINGHELM_KH-TYPE-C-16P
L1: 3.9nH; NORDIC_NRF_2_RESC0402_L
L2: 10µH; NORDIC_NRF_2_RESC0402_L
L3: 15nH; NORDIC_NRF_2_RESC0402_L
L5: 68uH; ESP32_C6_LIBRARY_2_IND_4828-WE-TPC_WRE
L7: FTC252012SR47MBCA; MLP2016SR47MT0S1_INDC2016X100N
Q1: 20V/4.2A/52mΩ/1.4W; ESP32_C6_LIBRARY_4_ESP32_C6_LIBRARY_4_ESP32_C6_LIBRARY_4_ES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
Q3: SI1308EDL-T1-GE3; ESP32_C6_LIBRARY_6_SOT65P210X110-3N
R1_EP_DR: 0.47; CPF0201D7K68C1_0201
R1_USB, R2_USB: 5K1; ERA-1AEB3401C_0201
R2, R3, R4: 0; CPF0201D7K68C1_0201
R2_EP_DR, R9: 10K; CPF0201D7K68C1_0201
R5, R7, R8: 10K; ERA-1AEB3401C_0201
R17, R18: 3K3; CPF0201D7K68C1_0201
R_PWR_EPD: 10K; CPF0201D7K68C1_0201
R_TYPE_SEL: 2.2; CPF0201D7K68C1_0201
SJ1: ESP32_C6_LIBRARY_7_JUMPER_SJ
SW_DN: 2025-10-22_07-23-44_LIBRARY_EVP-AKE31ASW_EVP-AKE3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; 2025-10-22_07-23-44_LIBRARY_SW_EVP-AKE31A_PAN
SW_ENT: 2025-10-22_07-23-44_LIBRARY_EVP-AKE31ASW_EVP-AKE3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; 2025-10-22_07-23-44_LIBRARY_SW_EVP-AKE31A_PAN
SW_UP: 2025-10-22_07-23-44_LIBRARY_EVP-AKE31ASW_EVP-AKE3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; 2025-10-22_07-23-44_LIBRARY_SW_EVP-AKE31A_PAN
TP_3.3V, TP_3V3: HECTOR_WATCH_1_TPTP20R; HECTOR_WATCH_1_TP20R
TP_BAT_GND: HECTOR_WATCH_1_TPTP20R; HECTOR_WATCH_1_TP20R
TP_GND: HECTOR_WATCH_1_TPTP20R; HECTOR_WATCH_1_TP20R
TP_ON: HECTOR_WATCH_1_TPTP20R; HECTOR_WATCH_1_TP20R
TP_OP: HECTOR_WATCH_1_TPTP20R; HECTOR_WATCH_1_TP20R
TP_RESET: HECTOR_WATCH_1_TPTP20R; HECTOR_WATCH_1_TP20R
TP_SCL: HECTOR_WATCH_1_TPTP20R; HECTOR_WATCH_1_TP20R
TP_SDA: HECTOR_WATCH_1_TPTP20R; HECTOR_WATCH_1_TP20R
TP_SW0: HECTOR_WATCH_1_TPTP20R; HECTOR_WATCH_1_TP20R
TP_SWDCLK: HECTOR_WATCH_1_TPTP20R; HECTOR_WATCH_1_TP20R
TP_SWDIO: HECTOR_WATCH_1_TPTP20R; HECTOR_WATCH_1_TP20R
TP_VBAT: HECTOR_WATCH_1_TPTP20R; HECTOR_WATCH_1_TP20R
TP_VREG: HECTOR_WATCH_1_TPTP20R; HECTOR_WATCH_1_TP20R
U1: NRF52840 _QF; NORDIC_NRF_4_AQFN50P700X700X85_HS-74N
U2: MAX17048G+T10; ESP32_C6_LIBRARY_SON50P200X200X80-9N
X1: 32MHz; NORDIC_NRF_BT-XTAL_2016_N
X2: 32.768kHz; NORDIC_NRF_1_XTAL_3215_N

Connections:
3V3/1.7D: C34.2, IC2.C2 (VDD), Q1.2 (S), R5.2, R7.2, R8.2, R_PWR_EPD.2
3V3/2.4A: C6.1, C7.1, C8.1, C12.1, C14.1, C19.1, C25.1, C33.1, IC3.3 (VDDIO), IC3.7 (VDD), IC3.10 (CSB), IC9.E2 (VOUT_1), IC9.E3 (VOUT_2), J2.1, R17.1, R18.1, TP_3.3V.TP, TP_3V3.TP, U1.P$A22 (VDD), U1.P$AD14 (VDD), U1.P$AD23 (VDD), U1.P$B1 (VDD), U1.P$W1 (VDD), U1.P$Y2 (VDDH)
ALERT/1.6C: U2.5 (!ALERT)
ALERT/2.5C: U1.P$J24 (P0.10/NFC2)
D+/1.5D: D3.4 (I/O2_2)
D+/2.7D: U1.P$AD6 (D+)
D-/1.5D: D3.6 (I/O1_2)
D-/2.7D: U1.P$AD4 (D-)
DN: D3.1 (I/O1_1), J4.A7 (DN1), J4.B7 (DN2)
DP: D3.3 (I/O2_1), J4.A6 (DP1), J4.B6 (DP2)
EPD_3V3: C1-EP-DR.1, EPD_C5.2, J1.15, J1.16, L5.2, Q1.3 (D)
EPD_BUSY/1.5D: J1.9
EPD_BUSY/2.2D: U1.P$AD12 (P0.17)
EPD_CS/1.4C: J1.12
EPD_CS/2.2D: U1.P$K2 (P0.05/AIN3)
EPD_DC/1.5D: J1.11
EPD_DC/2.2D: U1.P$AD10 (P0.15)
EPD_RST/1.5D: J1.10
EPD_RST/2.2D: U1.P$AC11 (P0.16)
GDR: J1.2, Q3.1 (G), R2_EP_DR.2
GND: C1.2, C1-EP-DR.2, C2.1, C3.2, C4.2, C5.2, C6.2, C7.2, C8.2, C9.2, C10.2, C11.2, C12.2, C13.2, C14.2, C15.2, C16.2, C17.1, C18.1, C19.2, C20.2, C21.2, C22.2, C23.1, C24.1, C25.2, C27.1, C29.1, C30.1, C31.1, C32.1, C33.2, C34.1, C37.1, C38.1, C39.2, C42.2, C43.2, D3.2 (GND), D4.1 (K), EPD_C1.1, EPD_C2.1, EPD_C5.1, EPD_C6.1, EPD_C7.1, EPD_C8.1, EPD_C9.1, EPD_C10.1, EPD_C11.1, EPD_C12.1, IC1.D2 (GND), IC2.B1 (IN/TRIG), IC2.B3 (GND), IC3.8 (GNDIO), IC3.9 (GND), IC9.B1 (VSEL), IC9.C1 (AGND), IC9.C2 (PGND_1), IC9.C3 (PGND_2), J1.8, J1.17, J1.MP1, J1.MP2, J2.3, J2.5, J4.A1_B12 (GND), J4.A12_B1 (GND), J4.SH1 (SHIELD), J4.SH2 (SHIELD), J4.SH3 (SHIELD), J4.SH4 (SHIELD), R1_USB.1, R2_EP_DR.1, R2_USB.2, R3.2, R9.1, R_TYPE_SEL.1, SJ1.1, SW_DN.1, SW_ENT.1, SW_UP.1, TP_BAT_GND.TP, TP_GND.TP, U1.P$74 (VSS_PAD), U1.P$75 (VSS_PAD), U1.P$76 (VSS_PAD), U1.P$77 (VSS_PAD), U1.P$78 (VSS_PAD), U1.P$79 (VSS_PAD), U1.P$80 (VSS_PAD), U1.P$81 (VSS_PAD), U1.P$82 (VSS_PAD), U1.P$83 (VSS_PAD), U1.P$84 (VSS_PAD), U1.P$85 (VSS_PAD), U1.P$86 (VSS_PAD), U1.P$87 (VSS_PAD), U1.P$88 (VSS_PAD), U1.P$89 (VSS_PAD), U1.P$90 (VSS_PAD), U1.P$B7 (VSS), U1.P$F23 (VSS_PA), U2.1 (CTG), U2.4 (GND), U2.6 (QSTRT), U2.9 (EP), X1.2, X1.4
HAPTIC_EN/1.4C: IC2.A1 (EN)
HAPTIC_EN/2.6A: U1.P$U1 (P0.12)
IMU_INT1: IC3.5 (INT1), U1.P$N1 (P0.08)
IMU_INT2: IC3.6 (INT2), U1.P$P2 (P1.08)
LX1: IC9.B2 (SW1_1), IC9.B3 (SW1_2), L7.1
LX2: L7.2
MOSI/1.5B: J1.14
MOSI/2.2D: U1.P$B13 (P0.03/AIN1)
unnamed: IC1.D1 (TS/MR), R9.2
unnamed: L2.1, U1.P$B3 (DCC)
unnamed: IC3.1 (SDO), R3.1
unnamed: L2.2, L3.1
unnamed: C10.1, C15.1, C16.1, L3.2, U1.P$B5 (DEC4), U1.P$E24 (DEC6)
unnamed: C13.1, U1.P$A18 (DEC2)
unnamed: C5.1, U1.P$C1 (DEC1)
unnamed: IC9.E1 (SDA), R2.1
unnamed: C17.2, U1.P$D2 (P0.00/XL1), X2.2
unnamed: IC9.D2 (SW2_1), IC9.D3 (SW2_2)
unnamed: IC9.D1 (SCL), R4.1
unnamed: C18.2, U1.P$F2 (P0.01/XL2), X2.1
unnamed: C20.1, U1.P$AC5 (DEC3V3)
unnamed: C9.1, U1.P$N24 (DEC5)
unnamed: C3.1, L1.1, U1.P$H23 (ANT)
unnamed: ANT1.1 (FEED), C4.1, C22.1, L1.2
unnamed: C11.1, U1.P$D23 (DEC3)
unnamed: C1.1, U1.P$B24 (XC1), X1.1
unnamed: C2.2, U1.P$A23 (XC2), X1.3
unnamed: C2-EP-DR.1, D2.1 (K), D4.2 (A)
unnamed: C2-EP-DR.2, D5.2 (A), L5.1, Q3.3 (D)
unnamed: R1_EP_DR.1, R_TYPE_SEL.2, SJ1.2
unnamed: C32.2, IC2.A2 (REG)
unnamed: J4.A5 (CC1), R1_USB.2
unnamed: J4.B5 (CC2), R2_USB.1
unnamed: EPD_C2.2, J1.4
unnamed: EPD_C1.2, J1.5
unnamed: EPD_C6.2, J1.18
unnamed: EPD_C7.2, J1.19
unnamed: EPD_C8.2, J1.20
unnamed: EPD_C10.2, J1.22
unnamed: EPD_C12.2, J1.24
OUT+: IC2.A3 (OUT+), TP_OP.TP
OUT-: IC2.C3 (OUT-), TP_ON.TP
P0.04: U1.P$J1 (P0.04/AIN2)
P0.09: U1.P$L24 (P0.09/NFC1)
P0.13/1.5D: C30.2, R5.1, SW_UP.2
P0.13/2.6C: U1.P$AD8 (P0.13)
P0.14/1.5D: C31.2, R8.1, SW_ENT.2
P0.14/2.7C: U1.P$AC9 (P0.14)
P0.19: U1.P$AC15 (P0.19)
P0.20: U1.P$AD16 (P0.20)
P0.21: U1.P$AC17 (P0.21)
P0.22: U1.P$AD18 (P0.22)
P0.23: U1.P$AC19 (P0.23)
P0.24: U1.P$AD20 (P0.24)
P0.25: U1.P$AC21 (P0.25)
P0.26: U1.P$G1 (P0.26)
P0.27: U1.P$H2 (P0.27)
P0.28: U1.P$B11 (P0.28/AIN4)
P0.29: U1.P$A10 (P0.29/AIN5)
P0.30: U1.P$B9 (P0.30/AIN6)
P0.31: U1.P$A8 (P0.31/AIN7)
P1.01/1.6C: Q1.1 (G), R_PWR_EPD.1
P1.01/2.4B: U1.P$Y23 (P1.01)
P1.02/1.6C: C29.2, R7.1, SW_DN.2
P1.02/2.8C: U1.P$W24 (P1.02)
P1.03: U1.P$V23 (P1.03)
P1.04: U1.P$U24 (P1.04)
P1.05: U1.P$T23 (P1.05)
P1.06: U1.P$R24 (P1.06)
P1.07: U1.P$P23 (P1.07)
P1.09: U1.P$R1 (P1.09)
P1.10: U1.P$A20 (P1.10)
P1.11: U1.P$B19 (P1.11)
P1.12: U1.P$B17 (P1.12)
P1.13: U1.P$A16 (P1.13)
P1.14: U1.P$B15 (P1.14)
P1.15: U1.P$A14 (P1.15)
PMIC_INT: IC1.A1 (!INT), U1.P$T2 (P0.11)
PREVGH: EPD_C9.2, J1.21
PREVGL: D2.2 (A), EPD_C11.2, J1.23
RESE: J1.3, Q3.2 (S), R1_EP_DR.2
RESET: J2.6, TP_RESET.TP, U1.P$AC13 (P0.18/RESET)
SCK/1.5B: J1.13
SCK/2.2D: U1.P$A12 (P0.02/AIN0)
SCL/1.4C: IC2.C1 (SCL), U2.7 (SCL)
SCL/2.4C: IC1.B1 (SCL), IC3.12 (SCX), R4.2, R17.2, TP_SCL.TP, U1.P$M2 (P0.07)
SDA/1.4C: IC2.B2 (SDA), U2.8 (SDA)
SDA/2.4C: IC1.C1 (SDA), IC3.2 (SDX), R2.2, R18.2, TP_SDA.TP, U1.P$L1 (P0.06)
SWDCLK: J2.4, TP_SWDCLK.TP, U1.P$AA24 (SWDCLK)
SWDIO: J2.2, TP_SWDIO.TP, U1.P$AC24 (SWDIO)
SWO: TP_SW0.TP, U1.P$AD22 (P1.00)
VBAT/1.2A: C27.2, TP_VBAT.TP, U2.2 (CELL), U2.3 (VDD)
VBAT/2.5C: C37.2, IC1.C2 (BAT)
VBUS/1.5D: C42.1, C43.1, D3.5 (VBUS), J4.A4_B9 (VBUS), J4.A9_B4 (VBUS)
VBUS/2.6D: C21.1, C38.2, IC1.A2 (IN), U1.P$AD2 (VBUS)
VREG: C23.2, C24.2, C39.1, IC1.B2 (SYS), IC9.A1 (EN), IC9.A2 (VIN_1), IC9.A3 (VIN_2), TP_VREG.TP

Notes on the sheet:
LiPo Charger
DC/DC
IMU
SWD
DEC1
P0.00/XL1
P0.00/XL2
DEC3
DEC4_6
Haptic Driver
Buttons
USB C Connector & ESD Protection
E-Paper Display Connector
Fuel Gauge
E-Paper Drive Circuit
DMG2305UX-7

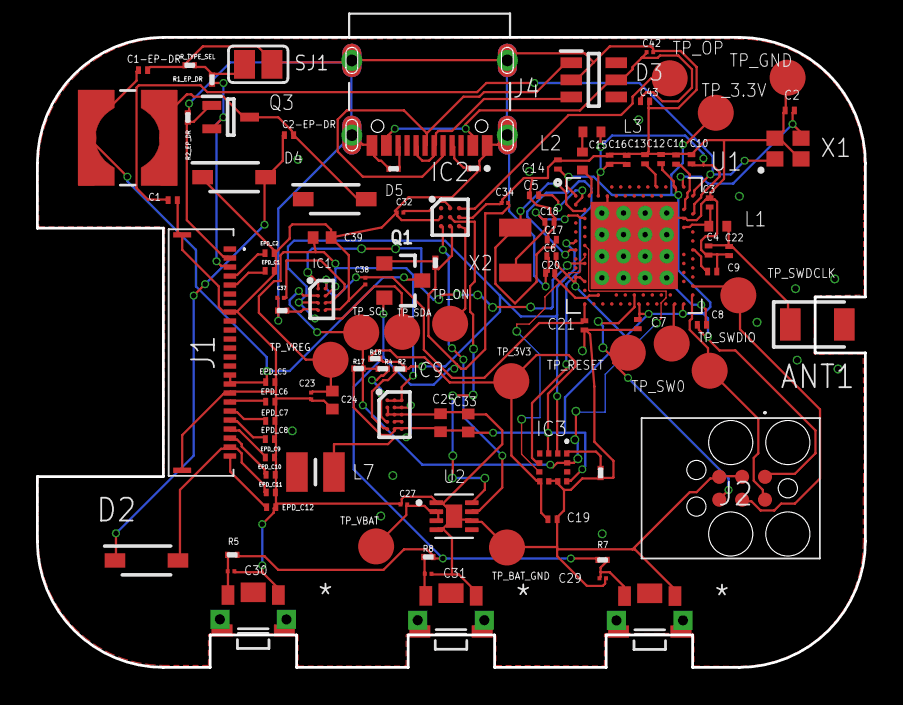
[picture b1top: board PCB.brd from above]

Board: 2 copper layers, 46.0 x 35.0 mm, 105 parts (0 on the bottom side), 65 nets.

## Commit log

2026-04-19 Add files via upload
    Am actualizat fisierul README cu modificarile cerute in issue (am adaugat descrierile care lipseau pentru anumite componente hardware).
2026-04-19 Add files via upload
    Am adaugat varianta .pdf a fisierului schematic
2026-04-19 Add files via upload
    Am adaugat label-urile pieselor care nu aveau deja, astfel incat sa am silkscreen-ul complet.

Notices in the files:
parts and their libraries:
COPYRIGHT: Copyright (C) 2024 Ultra Librarian. All rights reserved.
COPYRIGHT: Copyright (C) 2025 Ultra Librarian. All rights reserved.
